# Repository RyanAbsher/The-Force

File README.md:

# The-Force
 Raspberry Pi and Arduino Based Exhibit Show Controller
 
## Introduction
Shortly before we shut down operations due to Covid-19, one of the exhibits at my place of employment had a hardware failure. After we re-opened, due to financial hardships, we were unable
to cover the cost of having the exhibit repaired. It would require all new hardware as well as new software. I decided to see what I could do with the equipment on hand.

## Hardware

The exhibit uses 3 synchronized monitors to show a video, uses multiple DMX512 controlled lights, has an RS-232 controlled timer, and has multiple audio outputs. I decided to use 3 Raspberry Pis and
an Arduino Nano to replicate the original hardware.

I designed and etched a PCB that would hold the Arduino, as well as acting as the connection point for all of the different pieces. Each RPi has a cable which connects to this board. The DMX and RS-232 cables also plug into this board.
I put all of the requisite hardware for each of these protocols onboard.

For simply asthetic reasons I made the board fit the same form factor and mounting holes as a Raspberry Pi.

I laser cut the acrylic shelves and 3D printed the white plastic stand-offs.

## Software
When the user presses the start button, a python program on the center RPi detects it. It then signals the other 2 RPis to start the show on it's command. The center RPi also signals the Arduino to start the 
timer and begin the light show.

The timings for the light show require many entries into the Arduino program, and was too complicated to keep up with. I ended up creating a python program to help with that. I created a simle psuedo-scripting language (3 whole commands!) that allows me to create the light show in a more human-readable format. The python program then takes this input from def.txt, does all the math, and outputs the raw timings into def.h which can be used directly by the arduino program.

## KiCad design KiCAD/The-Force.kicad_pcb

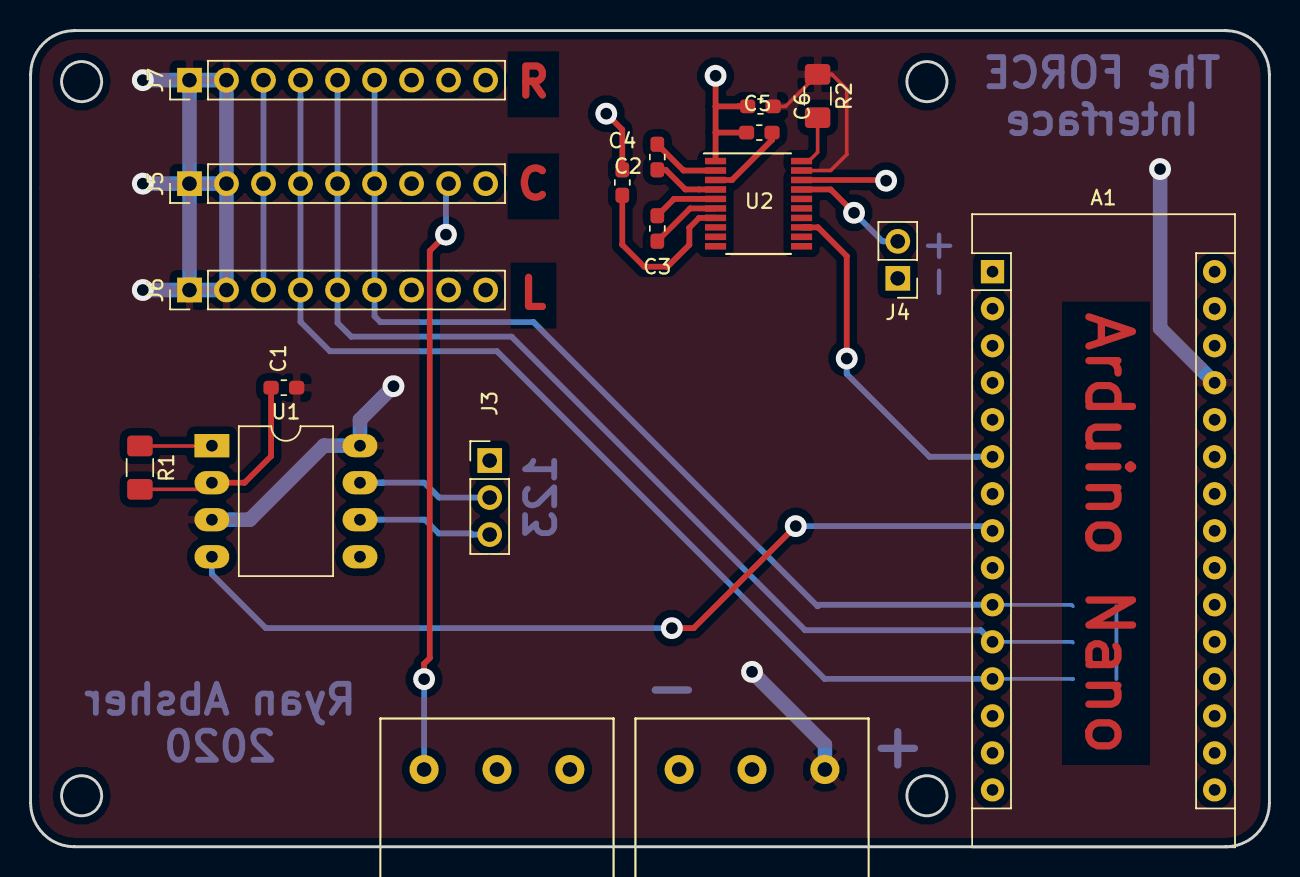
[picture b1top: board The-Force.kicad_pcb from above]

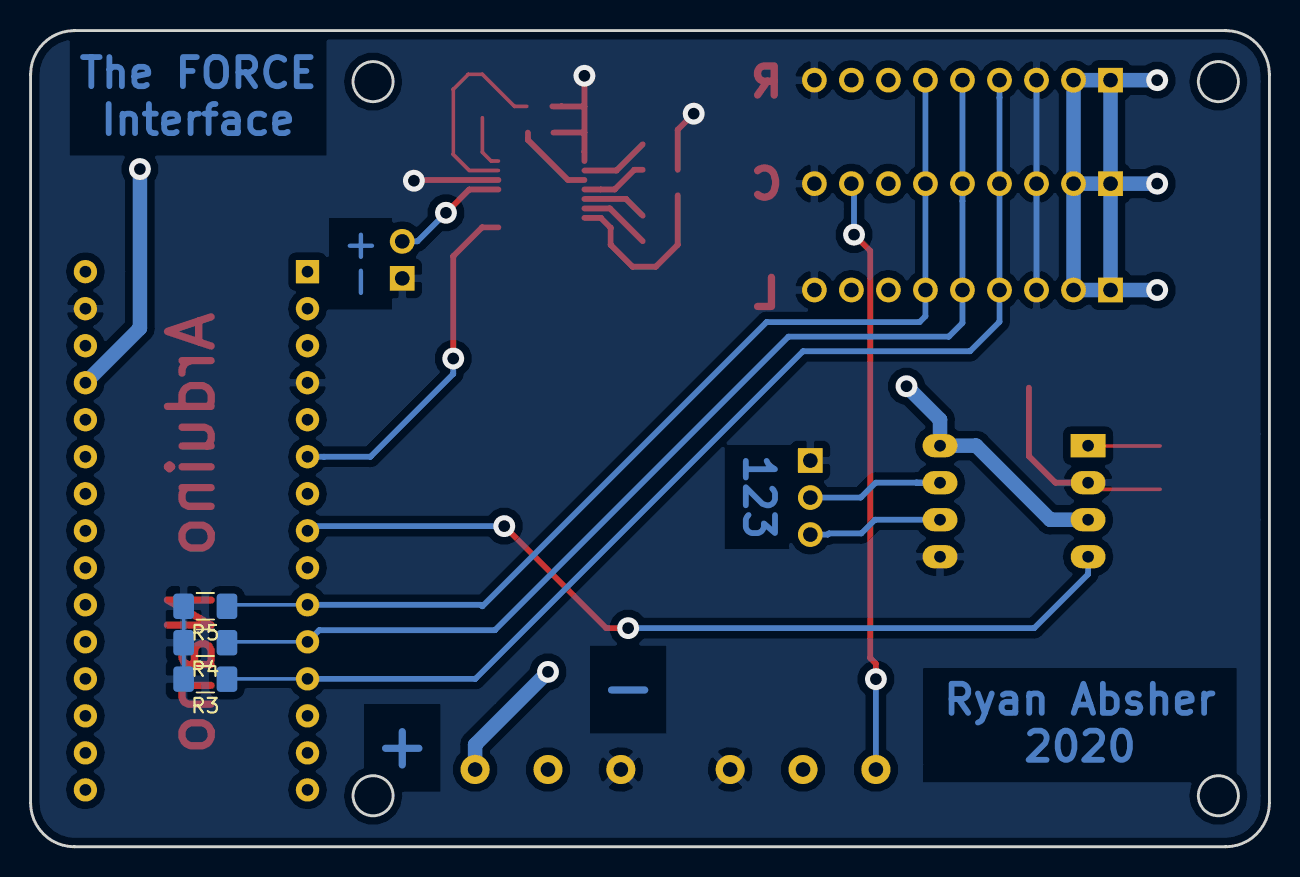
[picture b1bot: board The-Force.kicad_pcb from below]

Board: 2 copper layers, 85.0 x 56.0 mm, 21 parts (3 on the bottom side), 19 nets.

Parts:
A1: Arduino_Nano_v3.x; Arduino_Nano
C1, C6: 0.1uF; C_0603_1608Metric_Pad1.05x0.95mm_HandSolder
C2: 0.047uF; C_0603_1608Metric_Pad1.05x0.95mm_HandSolder
C3, C4, C5: 0.33uF; C_0603_1608Metric_Pad1.05x0.95mm_HandSolder
J1: Start Button; Terminal
J2: +5v In; Terminal
J3: XLR3_Ground; PinHeader_1x03_P2.54mm_Vertical
J4: To DB9; PinHeader_1x02_P2.54mm_Vertical
J5: RPi Center; PinHeader_1x09_P2.54mm_Vertical
J6: RPi Left; PinHeader_1x09_P2.54mm_Vertical
J7: RPi Right; PinHeader_1x09_P2.54mm_Vertical
R1: 100R; R_1206_3216Metric_Pad1.42x1.75mm_HandSolder
R2: 22k; R_1206_3216Metric_Pad1.42x1.75mm_HandSolder
R3, R4, R5: 20k; R_1206_3216Metric_Pad1.42x1.75mm_HandSolder
U1: SN75176AP; DIP-8_W10.16mm_LongPads
U2: MAX3222; TSSOP-20_4.4x6.5mm_P0.65mm

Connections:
+5V: A1.27, C1.2, C6.2, J2.3, J5.1, J5.2, J6.1, J6.2, J7.1, J7.2, R2.1, U1.3, U1.8, U2.19
/DMX/DMXA: J3.3, U1.6
/DMX/DMXB: J3.2, U1.7
/RS-232/RS232_OUT: J4.2, U2.17
/RS-232/V+: C5.2, U2.3
/START_BUTTON: J1.1, J5.8
DMX_DATA: A1.8, U1.4
GND: A1.4, A1.29, C1.1, C4.1, C5.1, C6.1, J1.3, J2.1, J3.1, J4.1, J5.3, J5.9, J6.3, J6.9, J7.3, J7.9, R1.2, R3.2, R4.2, R5.2, U1.2, U1.5, U2.1, U2.18
unnamed: C2.1, U2.4
unnamed: C2.2, U2.2
unnamed: C3.1, U2.6
unnamed: C3.2, U2.5
unnamed: C4.2, U2.7
unnamed: R1.1, U1.1
unnamed: R2.2, U2.20
RS_232_DATA: A1.6, U2.13
SHOW_SIGNAL_1: A1.12, J5.4, J6.4, J7.4, R3.1
SHOW_SIGNAL_2: A1.11, J5.5, J6.5, J7.5, R4.1
SHOW_SIGNAL_3: A1.10, J5.6, J6.6, J7.6, R5.1
